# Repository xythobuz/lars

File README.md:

# LARS - Looping Automated Rhythm Station

This is a simple drum machine / loopstation.
It's made for three hand-wound solenoids mounted to a tambourine.
It is controlled by a Raspberry Pi Pico on a custom PCB.

Please take a look at [the auto-generated documentation](https://xythobuz.github.io/lars/).

Also see [this blog post for some more context](https://www.xythobuz.de/lars.html).

## Quick Start

Initialize your local repo and prepare the build:

    git clone https://git.xythobuz.de/thomas/drumkit.git
    cd drumkit
    git submodule update --init
    cd pico-sdk
    git submodule update --init
    cd ..
    mkdir build
    cd build
    cmake ..
    cd ..

Then you can build new binaries like this:

    make -Cbuild -j4

For the first time, flash as usual using the mass storage bootloader (hold BOOTSEL while pluggin in the Pico).
After the firmware has been flashed once you can just use the included `flash.sh` to avoid having to hold the button.
Use `debug.sh` to open a serial console via USB.

## Documentation

You can find the [documentation here on GitHub pages](https://xythobuz.github.io/lars/).

The docs are built using [mdbook](https://github.com/rust-lang/mdBook), licensed as `MPL-2.0`.
Get the [latest release from GitHub](https://github.com/rust-lang/mdBook/releases) for a pre-built binary if you want to test changes to the docs locally.

    ./pcb/generate_plot.sh
    ./pcb2/generate_plot.sh
    ./3dprint/generate_stls.sh

    ./docs/generate_docs.sh serve

This will open your browser to a local development instance of the docs.

## Hardware Connections

These are the used pins on the first prototype.
Follow these if you want to build your own version without the included PCB design.

    Pin 1    GP0    I2C0 SDA
    Pin 2    GP1    I2C0 SCL

    Pin 29   GP22   Output Channel A
    Pin 31   GP26   Output Channel B
    Pin 32   GP27   Output Channel C

    Pin 34   GP28   Vbat (ADC2)

    Pin 11   GP8    Button 1
    Pin 12   GP9    Button 2
    Pin 16   GP12   Button 3
    Pin 19   GP14   Button 4

    Pin 22   GP17   Encoder A
    Pin 24   GP18   Encoder B
    Pin 21   GP16   Encoder Click

    Pin 14   GP10   LED 1
    Pin 15   GP11   LED 2
    Pin 17   GP13   LED 3
    Pin 20   GP15   LED 4

## License

The firmware of this project is licensed as GPLv3.
A copy of the license can be found in `COPYING`.

It uses the [Pi Pico SDK](https://github.com/raspberrypi/pico-sdk), licensed as BSD 3-clause, and therefore also [TinyUSB](https://github.com/hathach/tinyusb), licensed under the MIT license.

Some code is adapted from the TinyUSB examples.

To control the OLED display, [pico-ssd1306](https://github.com/daschr/pico-ssd1306) is used, licensed under the MIT license.

The code in `src/encoder.c` is derived from [mathertel/RotaryEncoder](https://github.com/mathertel/RotaryEncoder) and therefore licensed as BSD 3-clause.

Repo metadata is embedded into the project using [cmake-git-version-tracking](https://github.com/andrew-hardin/cmake-git-version-tracking), licensed under the MIT license.

The docs are built using [mdbook](https://github.com/rust-lang/mdBook), licensed as `MPL-2.0`.

The PCB SVG files in the documentation are displayed using [svg-pan-zoom](https://github.com/bumbu/svg-pan-zoom), licensed as `BSD-2-Clause`.

The 3D PCB files in the documentation are displayed using [three.js](hhttps://github.com/mrdoob/three.js), licensed as `MIT`.

Some code in `docs/src/js/3d.js` is derived from [a blog post of Michal Jirků](https://wejn.org/2020/12/cracking-the-threejs-object-fitting-nut/).

    This program is free software: you can redistribute it and/or modify
    it under the terms of the GNU General Public License as published by
    the Free Software Foundation, either version 3 of the License, or
    (at your option) any later version.

    This program is distributed in the hope that it will be useful,
    but WITHOUT ANY WARRANTY; without even the implied warranty of
    MERCHANTABILITY or FITNESS FOR A PARTICULAR PURPOSE.  See the
    GNU General Public License for more details.

    See <http://www.gnu.org/licenses/>.

The schematic and PCB design of this project is licensed under the [CERN Open Hardware Licence Version 2 - Strongly Reciprocal (CERN-OHL-S-2.0+)](https://ohwr.org/cern_ohl_s_v2.txt) or any later version.
A copy of the license can be found in `LICENSE`.

The PCB designs use a [KiCad-RP-Pico based](https://github.com/ncarandini/KiCad-RP-Pico) symbol and footprint library, licensed as `CC-BY-SA 4.0`.

The `pcb2/extern/EC12E-200.STEP` 3D model for the rotary encoder comes directly from the manufacturer, [ALPS](https://tech.alpsalpine.com/e/products/detail/EC12E24204A8/).

The `pcb2/extern/OLED_128x64.stp` 3D model for the SSD1306 OLED display is made by [
Adrián San José Torices](https://grabcad.com/library/pantalla-oled-0-96-128x64-1).

The SSD1306 footprint for pcb2 is from [KiCAD Rookie](https://kicadrookie.blogspot.com/2022/06/ssd1306-i2c-096in-oled-display-kicad_86.html).

The `pcb2/extern/5236AB/5236ab-41x408.stp` 3D model for the power switch comes directly from the manufacturer, [APEM](https://www.apem.com/idec-apem/de/Schalter-f%C3%BCr-Frontplatten/5000M/p/5236AB).

     ------------------------------------------------------------------------------
    | This source describes Open Hardware and is licensed under the CERN-OHL-S v2  |
    | or any later version.                                                        |
    |                                                                              |
    | You may redistribute and modify this source and make products using it under |
    | the terms of the CERN-OHL-S v2 (https://ohwr.org/cern_ohl_s_v2.txt)          |
    | or any later version.                                                        |
    |                                                                              |
    | This source is distributed WITHOUT ANY EXPRESS OR IMPLIED WARRANTY,          |
    | INCLUDING OF MERCHANTABILITY, SATISFACTORY QUALITY AND FITNESS FOR A         |
    | PARTICULAR PURPOSE. Please see the CERN-OHL-S v2 (or any later version)      |
    | for applicable conditions.                                                   |
    |                                                                              |
    | Source location: https://git.xythobuz.de/thomas/drumkit                      |
    |                                                                              |
    | As per CERN-OHL-S v2 section 4, should You produce hardware based on this    |
    | source, You must where practicable maintain the Source Location visible      |
    | on the external case of the Gizmo or other products you make using this      |
    | source.                                                                      |
     ------------------------------------------------------------------------------

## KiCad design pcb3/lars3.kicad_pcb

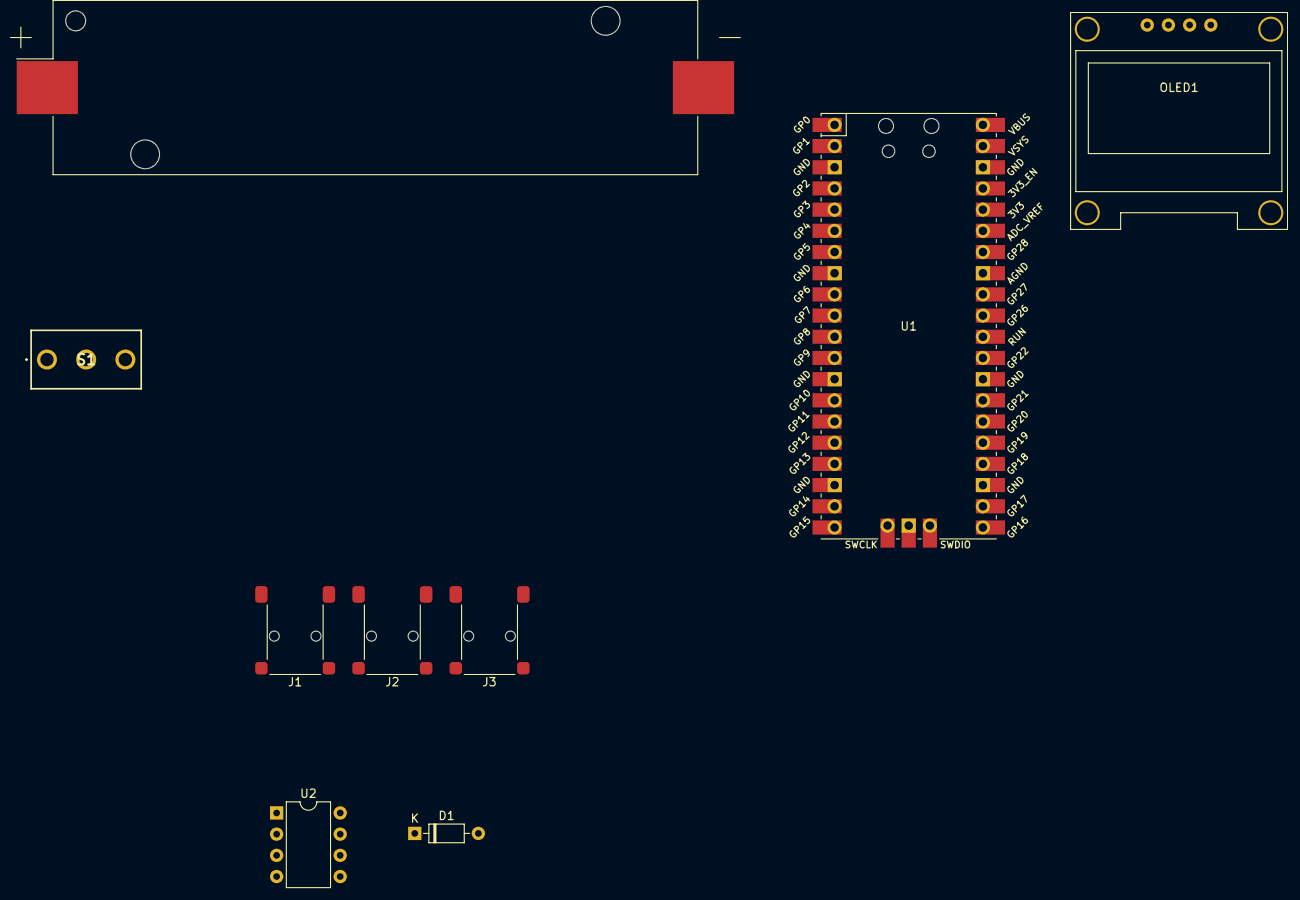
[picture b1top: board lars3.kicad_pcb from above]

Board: 2 copper layers, 9 parts (0 on the bottom side), 3 nets, no tracks yet.

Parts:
BT1: Battery_Cell; BatteryHolder_Keystone_1042_1x18650
D1: 1N914; D_DO-35_SOD27_P7.62mm_Horizontal
J1: MIDI IN; Jack_3.5mm_Lumberg_1503_02_Horizontal
J2: MIDI OUT; Jack_3.5mm_Lumberg_1503_02_Horizontal
J3: MIDI THRU; Jack_3.5mm_Lumberg_1503_02_Horizontal
OLED1: SSD1306; SSD1306_0.96_Oled
S1: 5236AB
U1: Pico; RPi_Pico_SMD_TH
U2: 6N138; DIP-8_W7.62mm

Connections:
GND: J2.S, J3.S, U2.5 (GND)
unnamed: D1.2 (A), J1.T, U2.3 (C2)
unnamed: D1.1 (K), U2.2 (C1)

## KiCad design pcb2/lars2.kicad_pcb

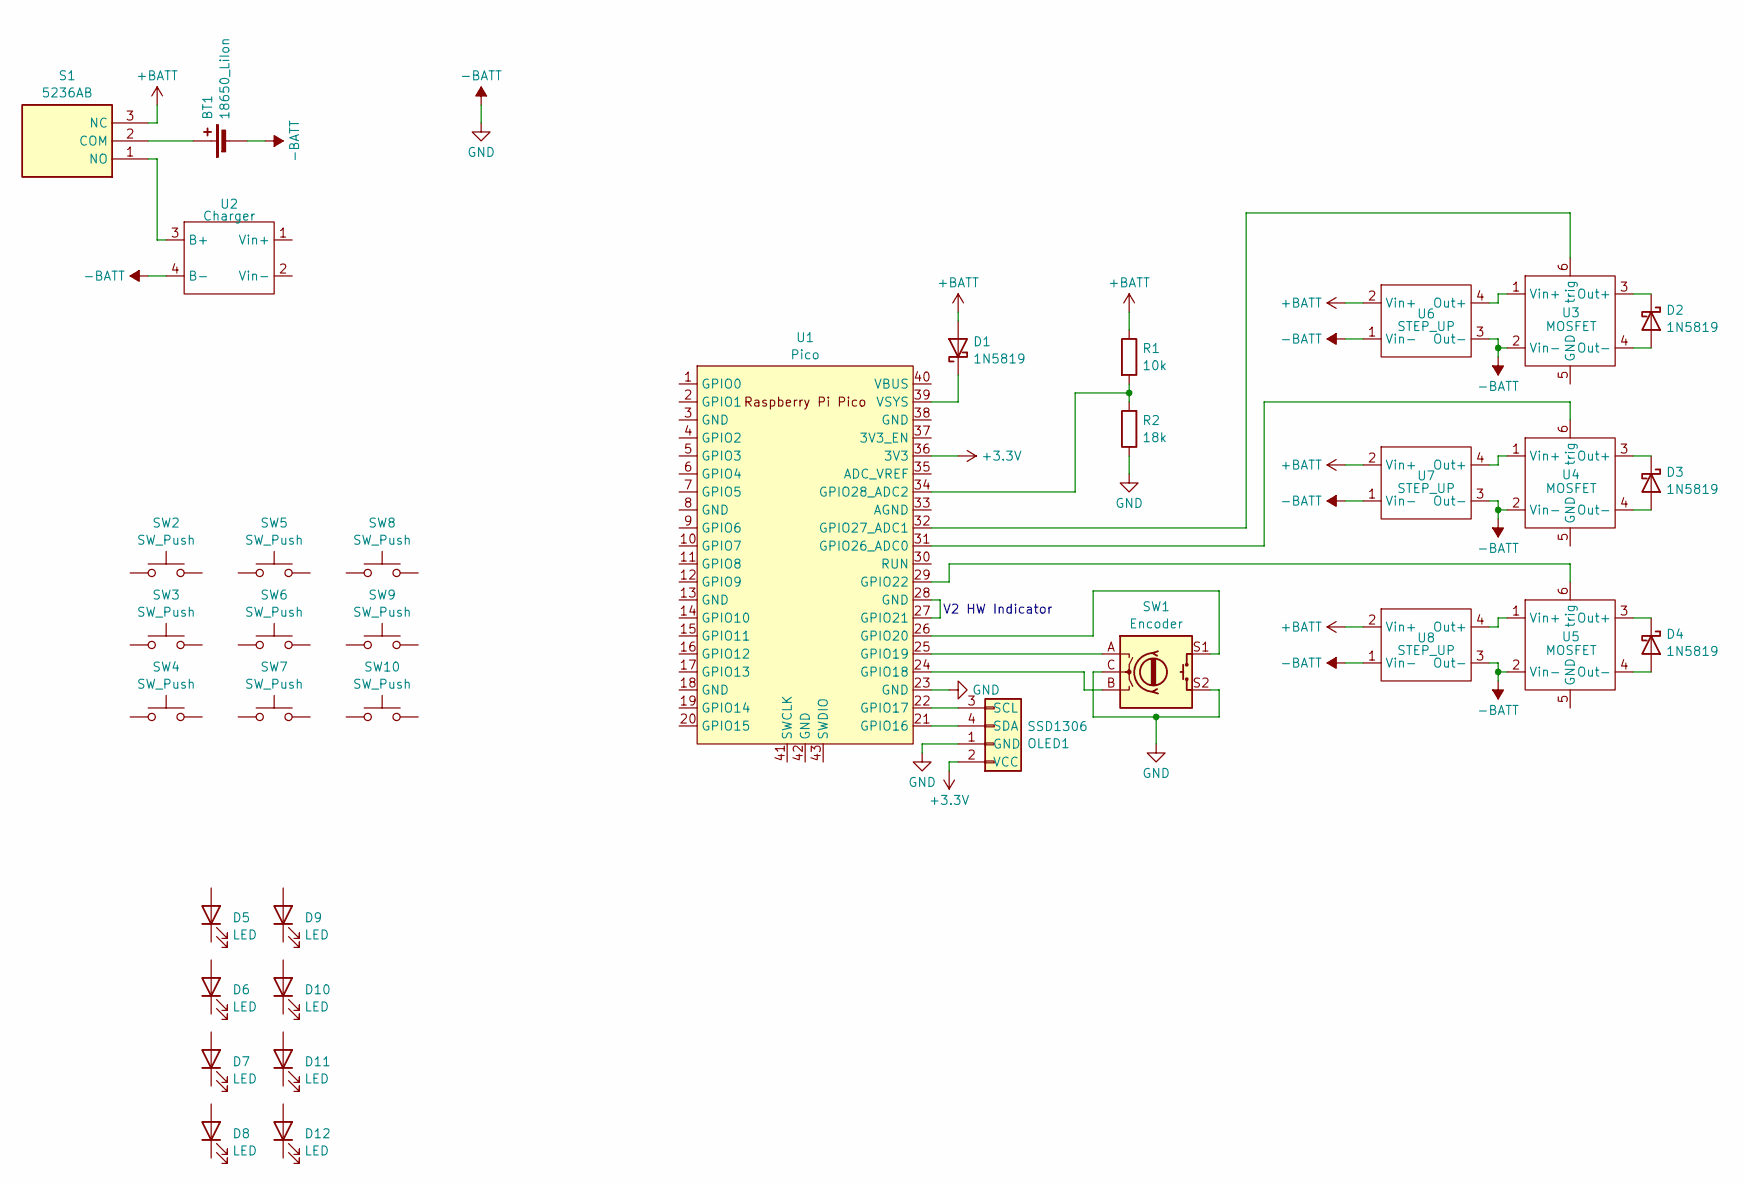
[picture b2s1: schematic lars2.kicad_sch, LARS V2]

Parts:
BT1: 18650_LiIon; BatteryHolder_Keystone_1042_1x18650
D1, D2, D3, D4: 1N5819; D_DO-41_SOD81_P10.16mm_Horizontal
D5, D6, D7, D8, D9, D10, D11, D12: LED; LED_D5.0mm
OLED1: SSD1306; SSD1306_0.96_Oled
R1: 10k; R_Axial_DIN0204_L3.6mm_D1.6mm_P2.54mm_Vertical
R2: 18k; R_Axial_DIN0204_L3.6mm_D1.6mm_P2.54mm_Vertical
S1: 5236AB; Manufacturer_Part_Number 5236AB
SW1: Encoder; RotaryEncoder_Alps_EC12E-Switch_Vertical_H20mm_CircularMoun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
SW2, SW3, SW4, SW5, SW6, SW7, SW8, SW9, SW10: SW_Push; SW_PUSH_6mm_H5mm
U1: Pico; RPi_Pico_SMD_only
U2: Charger; charger
U3, U4, U5: MOSFET; xy-mos
U6, U7, U8: STEP_UP; dc-dc module

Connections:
+3.3V: OLED1.2 (VCC), U1.36 (3V3)
+BATT: D1.2 (A), R1.1, S1.3 (NC), U6.2 (Vin+), U7.2 (Vin+), U8.2 (Vin+)
-BATT: BT1.2 (-), OLED1.1 (GND), R2.1, SW1.C, SW1.S2, U1.23 (GND), U2.4 (B-), U3.2 (Vin-), U4.2 (Vin-), U5.2 (Vin-), U6.1 (Vin-), U6.3 (Out-), U7.1 (Vin-), U7.3 (Out-), U8.1 (Vin-), U8.3 (Out-)
unnamed: BT1.1 (+), S1.2 (COM)
unnamed: D1.1 (K), U1.39 (VSYS)
unnamed: D2.2 (A), U3.4 (Out-)
unnamed: D2.1 (K), U3.3 (Out+)
unnamed: D3.2 (A), U4.4 (Out-)
unnamed: D3.1 (K), U4.3 (Out+)
unnamed: D4.2 (A), U5.4 (Out-)
unnamed: D4.1 (K), U5.3 (Out+)
unnamed: OLED1.3 (SCL), U1.22 (GPIO17)
unnamed: OLED1.4 (SDA), U1.21 (GPIO16)
unnamed: S1.1 (NO), U2.3 (B+)
unnamed: SW1.B, U1.24 (GPIO18)
unnamed: SW1.A, U1.25 (GPIO19)
unnamed: SW1.S1, U1.26 (GPIO20)
unnamed: U1.27 (GPIO21), U1.28 (GND)
unnamed: U1.29 (GPIO22), U5.6 (trig)
unnamed: U1.31 (GPIO26_ADC0), U4.6 (trig)
unnamed: U1.32 (GPIO27_ADC1), U3.6 (trig)
unnamed: R1.2, R2.2, U1.34 (GPIO28_ADC2)
unnamed: U3.1 (Vin+), U6.4 (Out+)
unnamed: U4.1 (Vin+), U7.4 (Out+)
unnamed: U5.1 (Vin+), U8.4 (Out+)

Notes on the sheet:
V2 HW Indicator

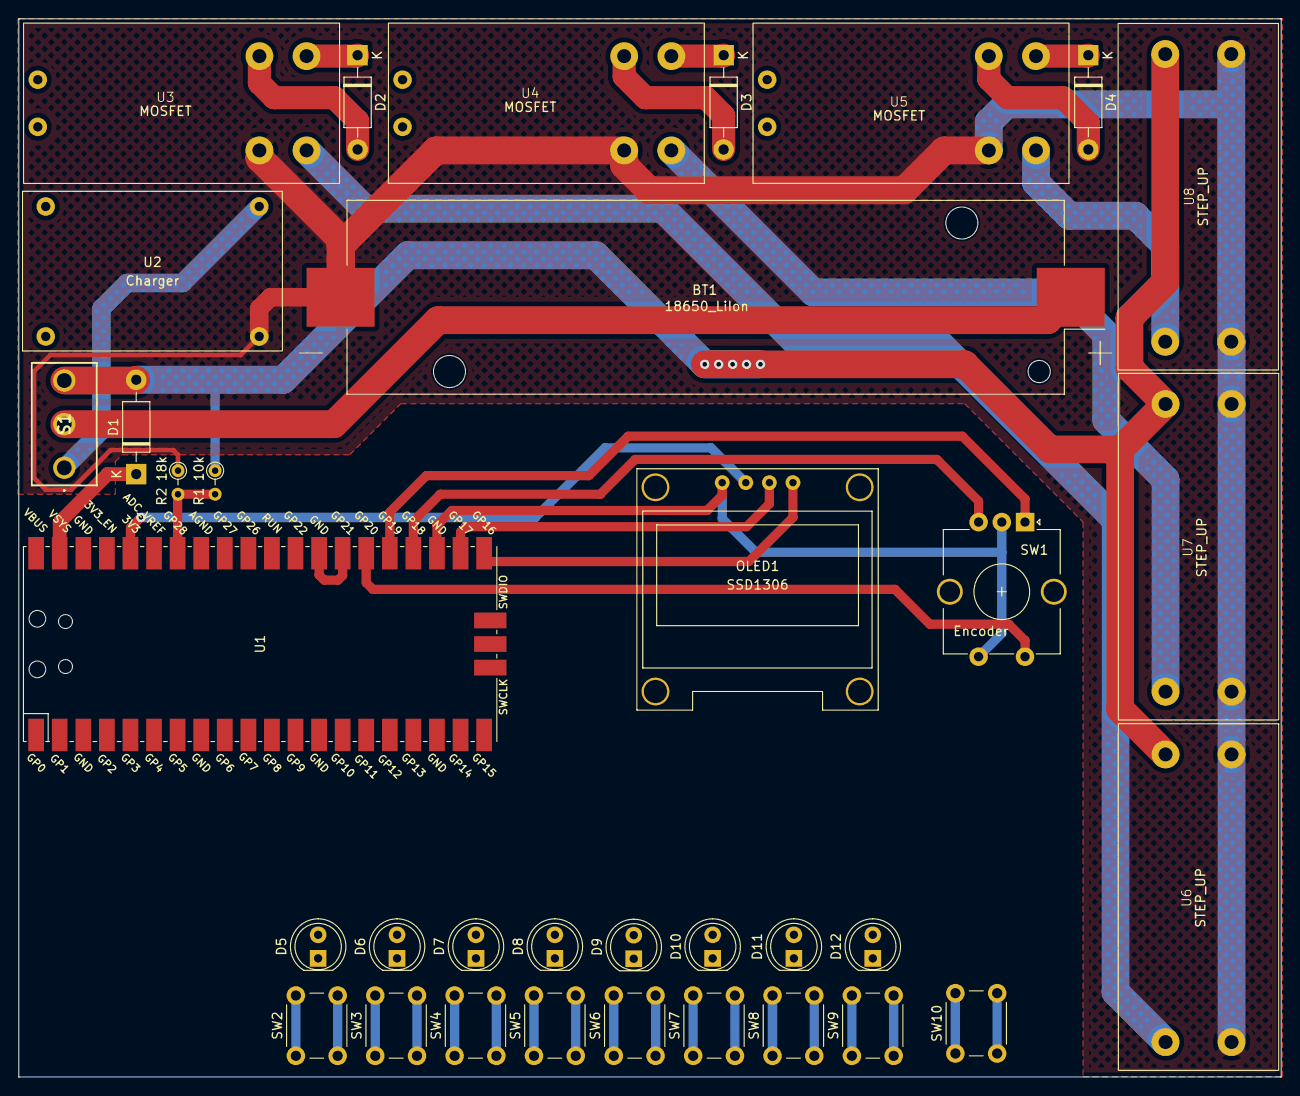
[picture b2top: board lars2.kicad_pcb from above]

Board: 2 copper layers, 136.0 x 114.0 mm, 35 parts (0 on the bottom side), 25 nets.

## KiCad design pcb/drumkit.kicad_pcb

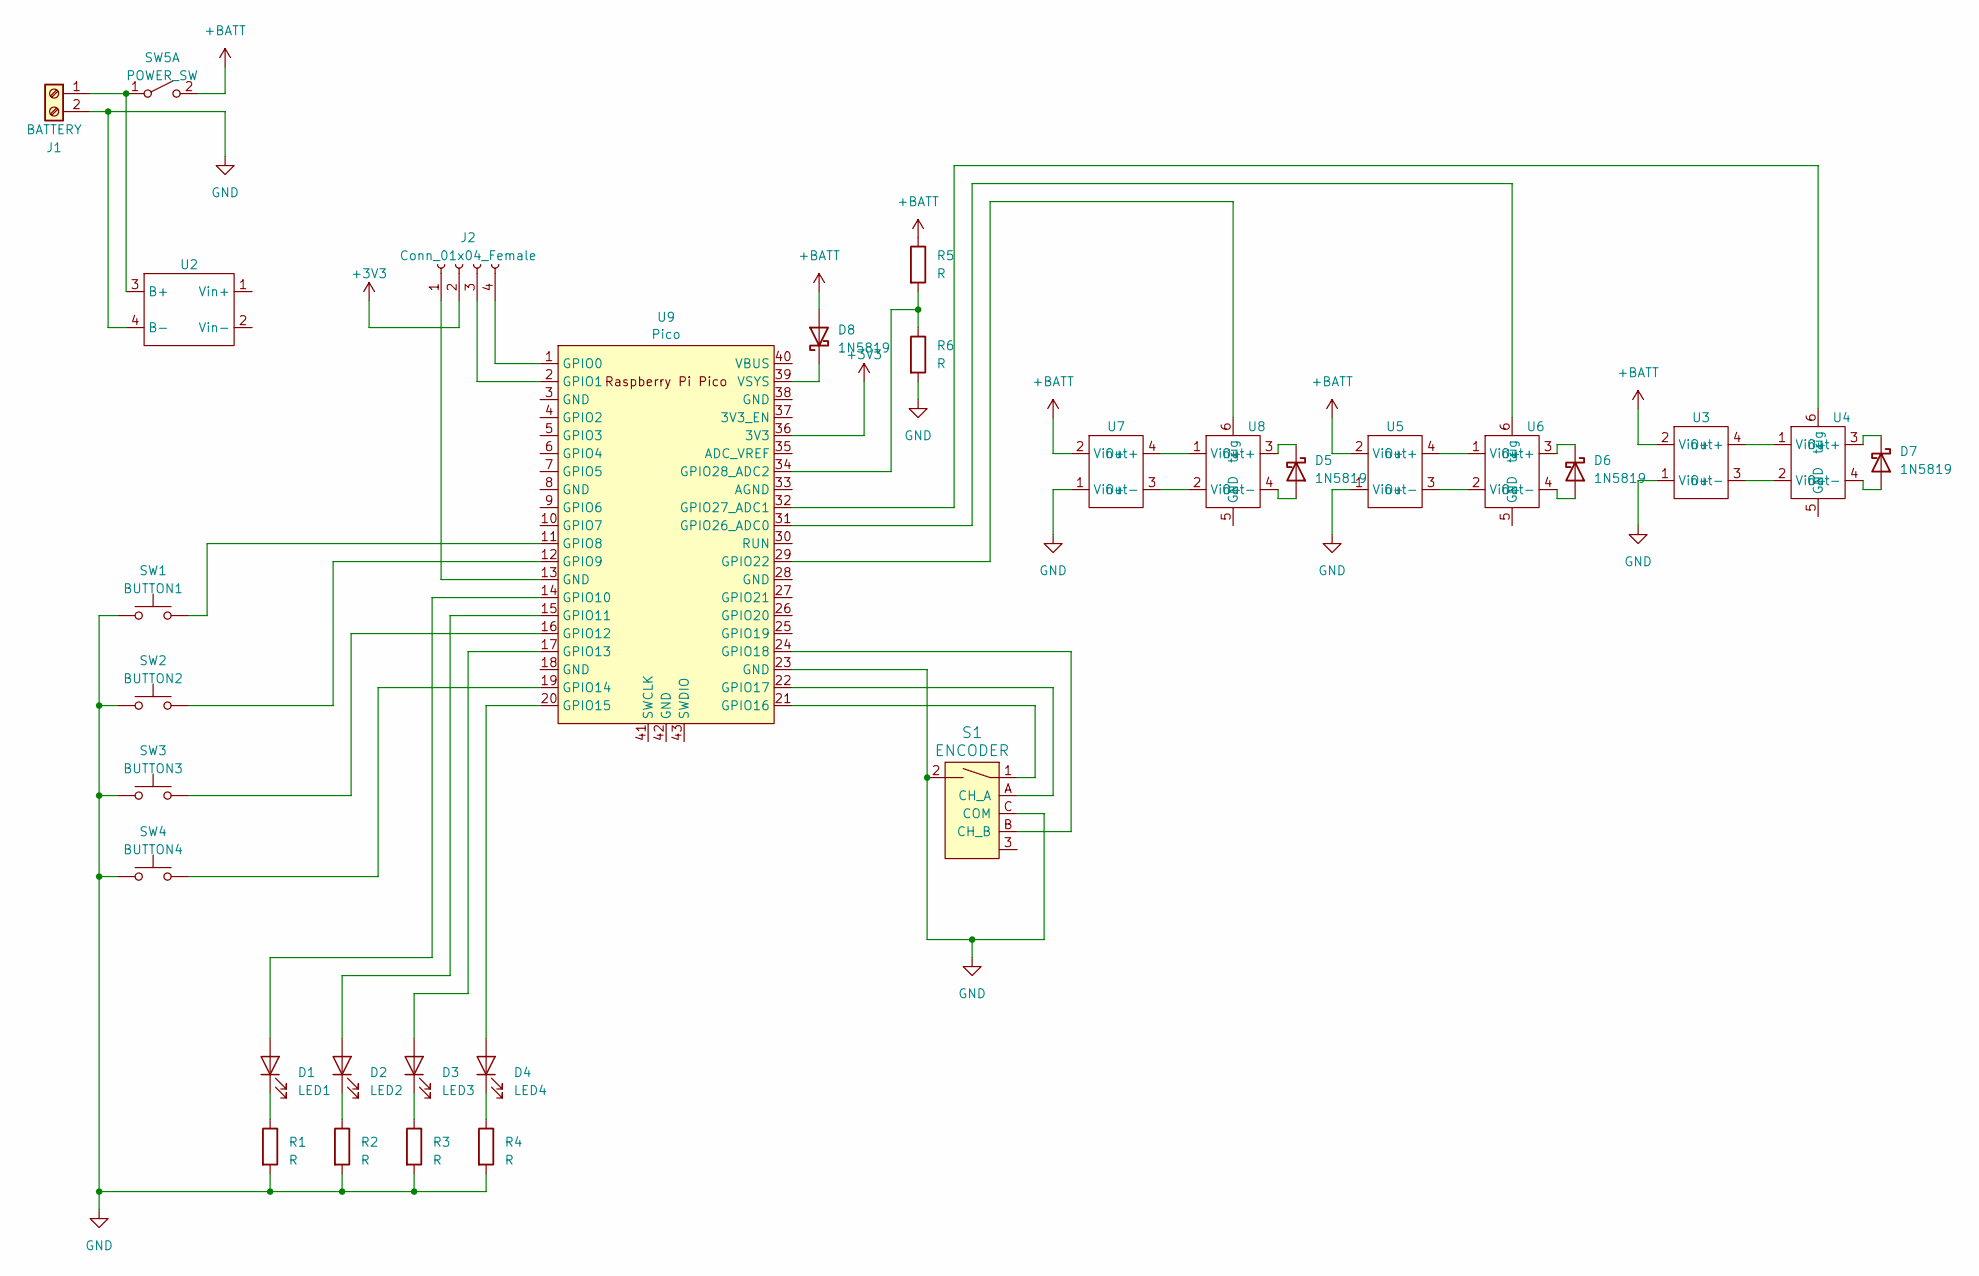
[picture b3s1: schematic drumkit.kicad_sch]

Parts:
D1: LED1; LED_D5.0mm
D2: LED2; LED_D5.0mm
D3: LED3; LED_D5.0mm
D4: LED4; LED_D5.0mm
D5, D6, D7, D8: 1N5819; D_DO-41_SOD81_P10.16mm_Horizontal
J1: BATTERY; TerminalBlock_bornier-2_P5.08mm
J2: Conn_01x04_Female; PinHeader_1x04_P2.54mm_Vertical
R1, R2, R3, R4: R; R_Axial_DIN0617_L17.0mm_D6.0mm_P5.08mm_Vertical
R5, R6: R; R_Axial_DIN0309_L9.0mm_D3.2mm_P12.70mm_Horizontal
S1: ENCODER; Rotary_Encoder_Switched_PEC11R; MPN PEC11R-4215F-S0024; Digi-Key_PN PEC11R-4215F-S0024-ND
SW1: BUTTON1; L_Radial_D12.0mm_P6.00mm_MuRATA_1900R
SW2: BUTTON2; L_Radial_D12.0mm_P6.00mm_MuRATA_1900R
SW3: BUTTON3; L_Radial_D12.0mm_P6.00mm_MuRATA_1900R
SW4: BUTTON4; L_Radial_D12.0mm_P6.00mm_MuRATA_1900R
SW5: POWER_SW; L_Radial_D12.0mm_P6.00mm_MuRATA_1900R
U2: charger
U3, U5, U7: dc-dc module
U4, U6, U8: xy-mos
U9: Pico; RPi_Pico_SMD_TH_noSWD

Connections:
+3V3: J2.2, U9.36 (3V3)
+BATT: D8.2 (A), R5.1, SW5.2 (B), U3.2 (Vin+), U5.2 (Vin+), U7.2 (Vin+)
GND: J1.2, R1.2, R2.2, R3.2, R4.2, R6.2, S1.2, S1.C (COM), SW1.1, SW2.1, SW3.1, SW4.1, U2.4 (B-), U3.1 (Vin+), U5.1 (Vin+), U7.1 (Vin+), U9.23 (GND)
unnamed: D1.2 (A), U9.14 (GPIO10)
unnamed: D1.1 (K), R1.1
unnamed: D2.2 (A), U9.15 (GPIO11)
unnamed: D2.1 (K), R2.1
unnamed: D3.2 (A), U9.17 (GPIO13)
unnamed: D3.1 (K), R3.1
unnamed: D4.2 (A), U9.20 (GPIO15)
unnamed: D4.1 (K), R4.1
unnamed: D5.2 (A), U8.4 (Out-)
unnamed: D5.1 (K), U8.3 (Out+)
unnamed: D6.2 (A), U6.4 (Out-)
unnamed: D6.1 (K), U6.3 (Out+)
unnamed: D7.2 (A), U4.4 (Out-)
unnamed: D7.1 (K), U4.3 (Out+)
unnamed: D8.1 (K), U9.39 (VSYS)
unnamed: J1.1, SW5.1 (A), U2.3 (B+)
unnamed: J2.1, U9.13 (GND)
unnamed: J2.3, U9.2 (GPIO1)
unnamed: J2.4, U9.1 (GPIO0)
unnamed: S1.A (CH_A), U9.22 (GPIO17)
unnamed: S1.B (CH_B), U9.24 (GPIO18)
unnamed: U3.4 (Out+), U4.1 (Vin+)
unnamed: U3.3 (Out-), U4.2 (Vin-)
unnamed: U4.6 (trig), U9.32 (GPIO27_ADC1)
unnamed: U5.4 (Out+), U6.1 (Vin+)
unnamed: U5.3 (Out-), U6.2 (Vin-)
unnamed: U6.6 (trig), U9.31 (GPIO26_ADC0)
unnamed: U7.4 (Out+), U8.1 (Vin+)
unnamed: U7.3 (Out-), U8.2 (Vin-)
unnamed: U8.6 (trig), U9.29 (GPIO22)
unnamed: SW1.2, U9.11 (GPIO8)
unnamed: SW2.2, U9.12 (GPIO9)
unnamed: SW3.2, U9.16 (GPIO12)
unnamed: SW4.2, U9.19 (GPIO14)
unnamed: S1.1, U9.21 (GPIO16)
unnamed: R5.2, R6.1, U9.34 (GPIO28_ADC2)

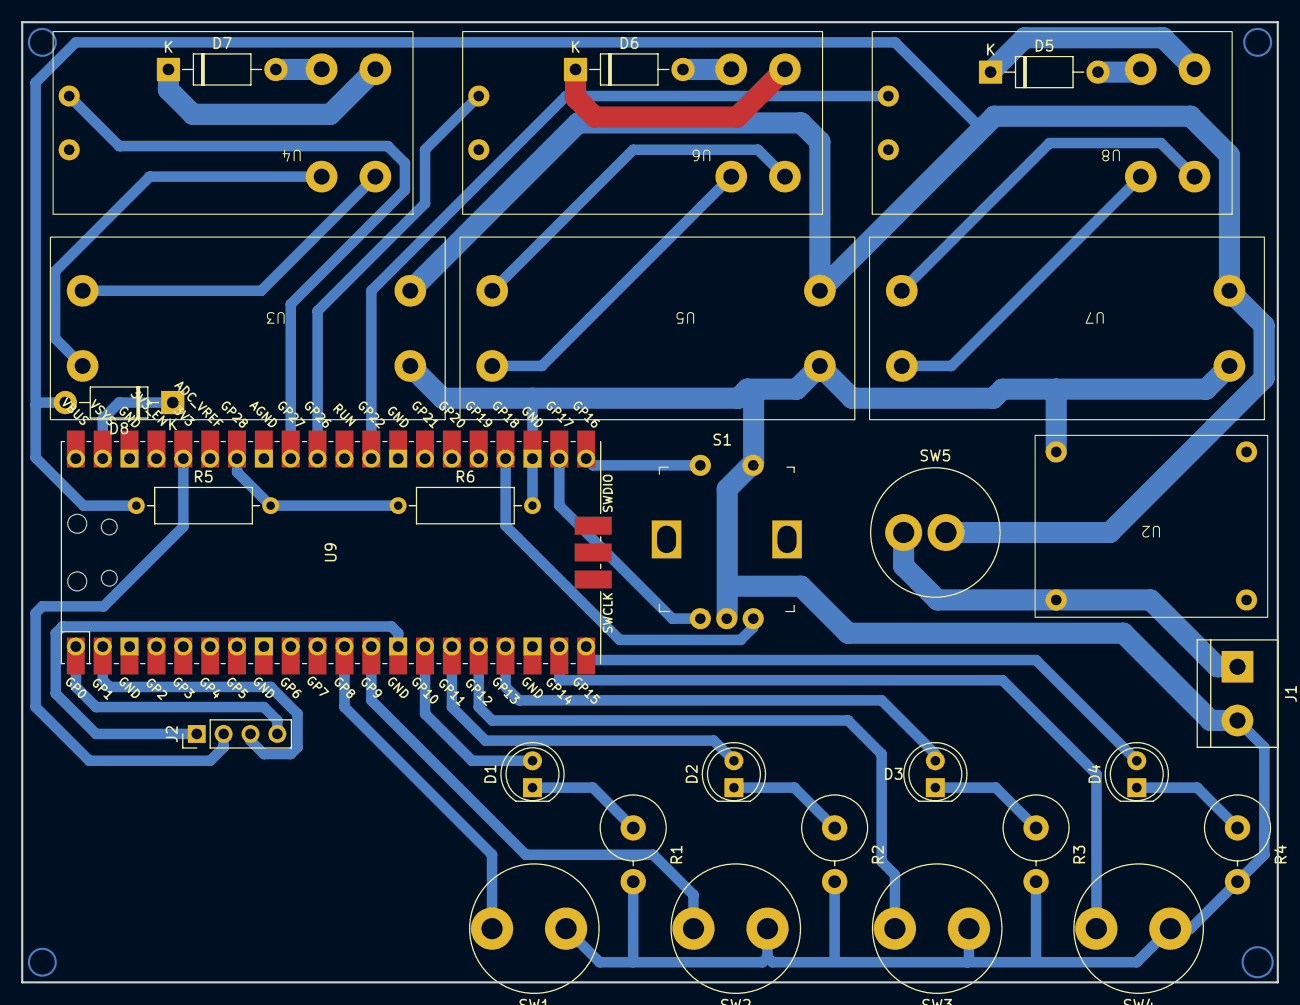
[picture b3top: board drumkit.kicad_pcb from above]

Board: 2 copper layers, 118.7 x 90.8 mm, 30 parts (0 on the bottom side), 39 nets.

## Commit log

2024-03-17 more stuff
2024-03-18 more untested code
2024-03-18 pass encoder moves to ui
2024-03-18 add turn off for gpio pulses
2024-03-19 start creating semiproper pcb
2024-03-21 fix board
2024-03-21 board ready kinda
2024-03-21 add voltage divider
2024-03-21 apdate pin assignment
2024-03-21 update pcb pdf
2024-03-21 ipdate buttons footprints
2024-03-21 fix button placement
2024-03-21 why is it not updating?
2024-03-22 cleanup and adjust pin numbers
2024-03-22 remove kicad backups from repo
2024-03-22 add link to dep
2024-03-22 mounting beam
2024-03-23 more 3d-printable parts
2024-03-23 cleanup, comments
2024-03-23 work on firmware
2024-03-23 more firmware
2024-03-23 machine now basically working
2024-03-24 usable faceplate
2024-03-24 pcb files cleanup
2024-03-25 cleanup pcb
2024-03-29 cleanup strange connection in schematic and pcb
2024-03-29 add cern license to pcb design. export diy pcb pdf.
2024-03-29 pcb under CERN license, in readme also.
2024-03-30 remove sensitive data
2024-03-30 start work on docs
2024-03-30 add gh workflows
2024-03-30 gh docs build
2024-03-30 squeeze in safety diodes
2024-03-30 remove STLs and add workflow to generate them
2024-03-30 scad workflow run apt update before install
2024-03-31 play around with three.js and stl and vrml loading
2024-03-31 more work on 3d viewer for docs
2024-03-31 generate incs for 3d visualizers
2024-03-31 add controls to docs 3d viewer
2024-03-31 auto center objects in 3d viewer
2024-03-31 enable anti aliasing in 3d viewer
2024-04-01 extend readme and status output
2024-04-01 add project for new pcb
2024-04-01 add 3d model to prototype pcb
2024-04-01 add more parts to pcb2
2024-04-01 add more parts for pcb2 and work on placement
2024-04-01 add ssd1306 oled to pcb2
2024-04-01 route pcb2 converters and outputs
2024-04-01 add power switch and finish output routing
2024-04-01 add batt- plane
2024-04-01 add battery voltage divider to pcb2
2024-04-01 add second ground plane
2024-04-01 finish pcb2, now with buttons and leds
2024-04-01 add links to gerbers in docs
2024-04-02 add BOMs, better lighting for 3d.js vrml
2024-04-11 add logo
2024-04-12 wip lars v2 fw
2024-04-12 implement button matrix reading
2024-04-12 small tweaks
2024-04-12 print bat percent
2024-04-12 add firmware workflow for gh actions
2024-04-13 split docs 3d print page
2024-04-13 wip print version
2024-04-17 more low pass filtering for battery voltage
2024-04-28 add MIDI support
2024-04-28 add midi tx
2024-04-28 add version info to built fw
2024-04-28 add some usage notes to docs
2024-04-28 fix some ui bugs
2024-04-28 lcd presence detection
2024-04-29 add configuration storage in flash
2024-04-29 tweaks
2024-04-29 allow triggering channels in settings mode
2024-04-29 fix some scrolling issues
2024-04-29 add some basic scaling of encoder value according to turning velocity
2024-04-29 add picture of v2 pcb to docs
2024-04-29 drum machine mode now kinda usable
2024-05-14 lars2 revision 2: use tht footprint for pi pico. improve optics of schematics matrix wiring.
2024-05-16 start work on pcb3 midi interface
2024-05-18 some hints on what to implement next
2024-05-18 add channel muting in loop station
2025-05-03 implement missing loop station features. update pico-sdk. other small improvements. mark as release 1.0.
2025-05-03 fix for ci
2025-05-03 fix for ubuntu missing type print macros
2025-05-03 try again to fix for ubuntu gcc
2025-05-03 add pwm led brightness control. fix led pins for prototype hardware.

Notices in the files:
pcb/drumkit.kicad_pcb:
Licensed under the CERN-OHL-S-2.0+
Copyright (c) 2024 Kauzerei, Thomas Buck
pcb2/lars2.kicad_pcb:
Copyright (c) 2024 Thomas Buck, Kauzerei
